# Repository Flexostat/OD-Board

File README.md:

# OD-Board
This repository contains the optical density measurement PCB and firmware source
 and production files for the Flexostat and syphonstat.

### Production_files/PCB/
These are the files that get zipped and sent to the PCB fabricator.

### Production_files/firmware.hex
This is the firmware file to be loaded onto the OD board.  

### seeed_bom.csv
This is the BOM file used by Seeedstudio to assemble the PCB.  If assembled by
Seeedstudio, the light sensors still need to be added afterwards since seeed
does not stock them.

<br />This work is licensed under a <a rel="license" href="http://creativecommons.org/licenses/by/4.0/">Creative Commons Attribution 4.0 International License</a>.

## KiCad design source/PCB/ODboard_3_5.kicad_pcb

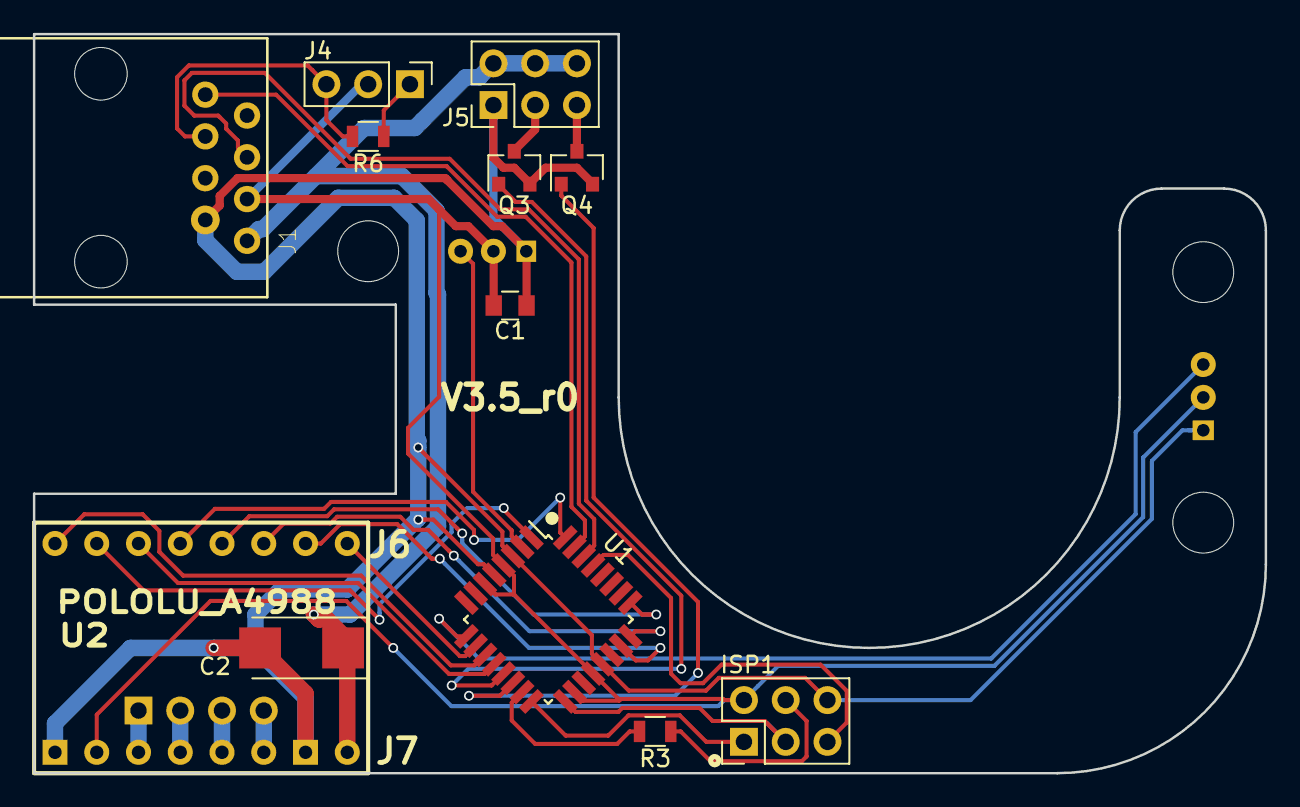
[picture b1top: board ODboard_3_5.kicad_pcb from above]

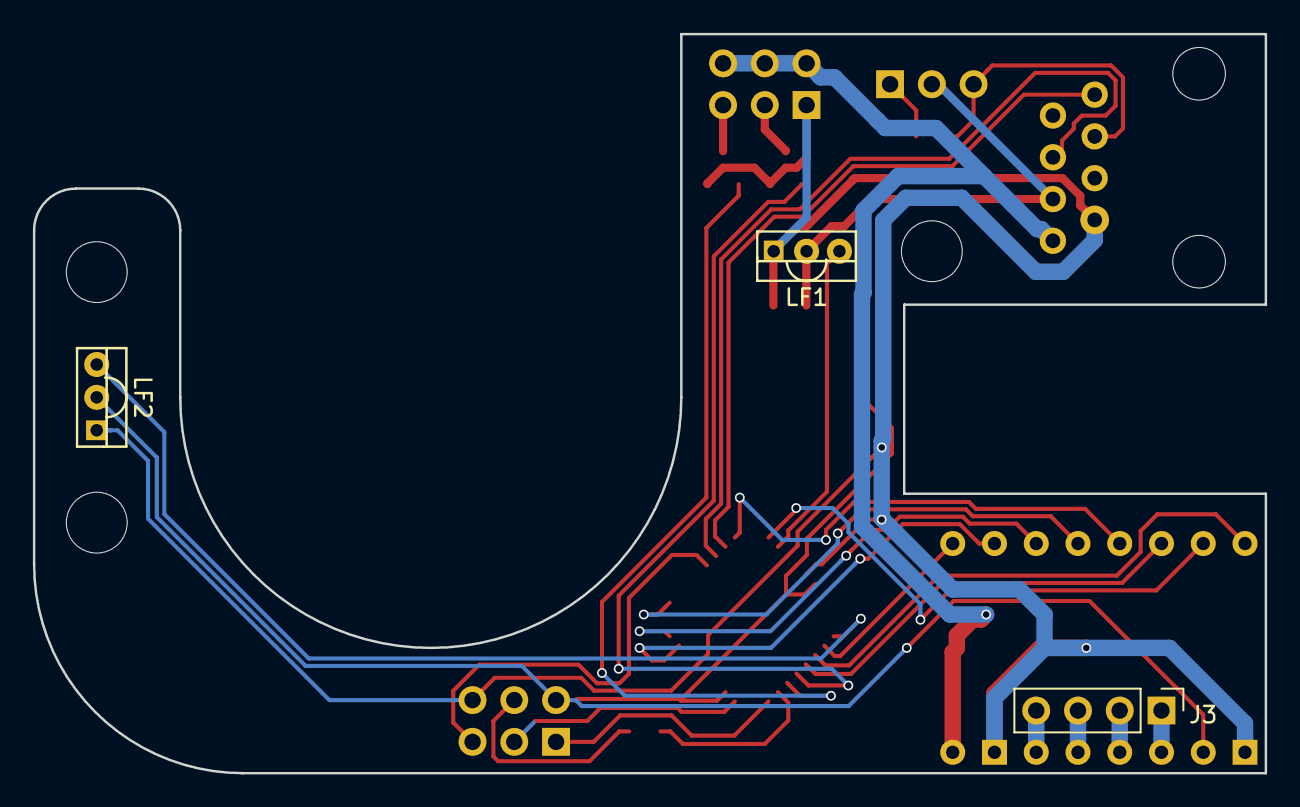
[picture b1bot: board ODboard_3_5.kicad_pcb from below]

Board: 2 copper layers, 74.9 x 45.0 mm, 15 parts (3 on the bottom side), 30 nets.

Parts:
C1: 1uF; C_0805
C2: 47uF; CP_Tantalum_Case-C_EIA-6032-28_Reflow
ISP1: AVR-ISP-6; Pin_Header_Straight_2x03_Pitch2.54mm
J1: RJ45; 54602-908LF
J3: CONN_01X04; Pin_Header_Straight_1x04_Pitch2.54mm
J4: CONN_01X03; Pin_Header_Straight_1x03_Pitch2.54mm
J5: CONN_02X03; Pin_Header_Straight_2x03_Pitch2.54mm
LF1, LF2: TSL235R-LF; TSL235R-LF-S
Q3, Q4: CJ2302; SOT-23
R3, R6: 10k; R_0805
U1: ATMEGA328P-A; TQFP-32_7x7mm_Pitch0.8mm
U2: POLOLU_A4988; SWDIP8_.6W

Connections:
+5V: C1.1, ISP1.2, J1.6, J4.2, LF1.2, LF2.2, U1.4, U1.6, U1.18, U1.20, U2.2
+12V: C2.1, J1.8, J5.2, J5.4, J5.6, U2.8
/LF1: LF1.3, U1.2
/LF2: LF2.3, U1.9
/M!EN: U1.10, U2.9
/M!RST: U1.32, U2.13
/M!SLP: U1.12, U2.14
/MDIR: U1.11, U2.16
/MISO: ISP1.1, U1.16
/MS1: U1.23, U2.10
/MS2: U1.24, U2.11
/MS3: U1.25, U2.12
/OC2A: R3.2, U1.15
/OC2B: U1.1, U2.15
/PB1: Q3.1, U1.13
/PB2: Q4.1, U1.14
/SCK: ISP1.3, U1.17
/S_RX: J1.4, U1.30
/S_TX: J1.1, U1.31
/rst: ISP1.5, U1.29
GND: C1.2, C2.2, ISP1.6, J1.7, J5.1, LF1.1, LF2.1, Q3.2, Q4.2, U1.3, U1.5, U1.21, U2.1, U2.7
unnamed: ISP1.4, R3.1
unnamed: J1.3, J4.3, R6.2
unnamed: J3.1, U2.3
unnamed: J3.2, U2.4
unnamed: J3.3, U2.5
unnamed: J3.4, U2.6
unnamed: J4.1, R6.1
unnamed: J5.3, Q3.3
unnamed: J5.5, Q4.3

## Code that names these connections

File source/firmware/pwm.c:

/*
 * pwm.c
 *
 * Created: 8/2/2011 3:10:29 PM
 *  Author: soslab
 */ 
#include "pwm.h"
#include "EEMAP.h"
#include <avr/io.h>
#include <avr/interrupt.h>
#include <avr/eeprom.h>

volatile uint16_t millist;
volatile uint16_t ust;
volatile uint16_t us_p_int;

//setup stir motor PWM
//TODO: convert this to work with timer2
void pwm_init() {
	/******STIR INIT*******/

	DDRD |= 0x08; //PD3:OSC2B output
	DDRD |= 0x04; //PD2 -> !MRST
	DDRD |= 0x40; //PD6 -> !MEN
	DDRD |= 0x80; //PD7 -> MDIR
	DDRB |= 0x01; //PB0 -> !MSLP
	DDRC |= 0x07; //PC0-PC2 output  -> MS1-MS3
	/************************************************************************/
	/*
	MS1 	MS2 	MS3 	Microstep Resolution
	Low 	Low 	Low 	Full step
	High	Low 	Low 	Half step
	Low 	High	Low 	Quarter step
	High	High	Low 	Eighth step
	High	High	High	Sixteenth step                                  */
	/************************************************************************/
	uint8_t stepmode = eeprom_read_byte(EE_ADDR_STEP);
	stepmode = stepmode == 0xff ? 0 : stepmode &0x07;  //take default full steps, mask lower 3 bits
	PORTC &= ~0x07; //PC0-PC2 low = full step
	PORTC |= stepmode;
	//PORTC |= 0x01; //half step
	PORTD |= 0x04; //pull motor reset high
	PORTD &= ~0x40; //pull motor enable low
	PORTB |= 0x01; //pull motor sleep high
	
	
	//CTC mode, toggle on compare match  B
	TCCR2A = 0x02 | 0x10; 
	//cksel /256,
	TCCR2B = 0x06;
	
	//toggle on counter top/2  
	//OCR2A = COUNTER_TOP/2;
	uint8_t ctop = eeprom_read_byte(EE_ADDR_COUNT);
	ctop = (ctop>32 && ctop<=64) ? ctop : COUNTER_TOP;
	OCR2A = ctop;
	us_p_int = (COUNTER_TOP+1)*(256/8);
	OCR2B = 0;
	
	TIMSK2 = 1<<OCIE2A; 
	
}

//one epoch is 2/STIR_SPEED seconds
//takes roughly 120 cycles every US_PER_INT
ISR (TIMER2_COMPA_vect) { 
  ust += us_p_int;
  while (ust>1000) {
	  ust-=1000;
	  millist +=1;
  }
}

uint16_t millis() {
  return millist;
}

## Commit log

2013-03-06 added firmware code
2014-03-18 added eagle files for LED board. version 3.1
2014-03-18 updated to version 3.2 of led PCB
2014-03-19 added BOM file for ordering LED board from seeed studio preassembled
2014-03-19 first test port to new ATMEGA part. should also compile for old 164 part
2014-03-19 added error check at complie time
2014-04-04 added support for LED board version 3.2
2014-04-04 Updated PCB design for ledboard 3.2r1
2014-05-13 reorg directory structure
2014-05-13 more file reorg
2014-05-13 updated c code to reflect new boards. included hex file
2014-08-07 LED board update rev3. Vs and Vss corrected
2014-11-18 fixed whitespace
2014-12-19 millis now counts the full range of uint16_t.
2014-12-19 tabs->spaces. And added PV pulse support on B1
2014-12-19 added syphonstat binary
2014-12-19 now pulls enable pin high for stirring on newest board rev
2015-08-12 added control over stirrer driver OE
2015-08-12 updated bom file for seeed's new format
2015-08-28 fixed bom to align with seeed's new partnumber
2015-09-08 soldering jig
2015-09-30 fixed partnumber changed by seeed
2016-01-23 added back text files
2016-01-23 file structre reorg
2016-01-23 updated PCB
2016-01-23 forgot this in the last push
2016-01-23 fixed file name reference
2016-01-23 updated code to match PCB 3.3
2016-01-23 updated production firmware
2016-02-11 updated footprint for rj45
2016-03-31 updated pcb -- untested!
2017-05-12 updated pcb with better motor drivers -- tested and working.
2017-07-01 updated BOM.
2017-07-01 Fixed two bugs that canceled each other out, as well as removed some dead code.
2017-07-01 more cleanup and added to .gitignore
2017-07-01 added adjustable RPM
2017-08-14 new firmware for speed control
2017-08-22 ignore build dirs
2017-08-22 Redesign from scratch. in KiCAD new design should be easier to assemble and leaves room for better laser alignment
2017-09-01 BOM had M instead of F pin headers for stepper driver
2019-08-23 added kicad temp files
2019-08-23 update to kicad 5
2020-03-09 changed license to CC-BY
2020-03-09 changed to CC-BY
